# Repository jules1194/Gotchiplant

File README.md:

# Gotchiplant
Este proyecto busca implementar las funciones de una planta inteligente.

## Diagrama de caja negra sin solución tecnológica

## Diagrama de caja negra tecnológico

## Diseños realizados en clase

## Implementación 

### Esquematico circuital Gotchiplant

### Ruteo de las pistas en Kicad

### Diseño de la PCB en 3D

### PCB Real Terminada

## Pruebas realizadas durante la ejecución del proyecto

### Prueba Lectura de datos Arduino IDE  y salida Display
https://github.com/jules1194/Gotchiplant/assets/137961658/6f60a92b-0001-46fb-bf46-45bb00d068b1

### Conexión sensores y Arduino Nano a la PCB

### Prueba Simulación Código en Arduinio IDE
https://github.com/jules1194/Gotchiplant/assets/137961658/443aca30-f3b6-4041-8bca-e2bd3c89cd1e

### Prueba ensamble sensores, arduino nano y PCB con alimentación externa
https://github.com/jules1194/Gotchiplant/assets/137961658/406dce42-54d8-423b-a3e7-269711841c6a

## Videos sobre la implementación final del proyecto

### Explicación sobre la ubicación de los sensores de Gotchiplant
https://github.com/jules1194/Gotchiplant/assets/137961658/88809492-0296-4c42-850c-8ad4974c118a

### Funcionamiento Gotchiplant
https://github.com/jules1194/Gotchiplant/assets/137961658/c117f062-664b-49f6-9f2e-c704b0ddebe9

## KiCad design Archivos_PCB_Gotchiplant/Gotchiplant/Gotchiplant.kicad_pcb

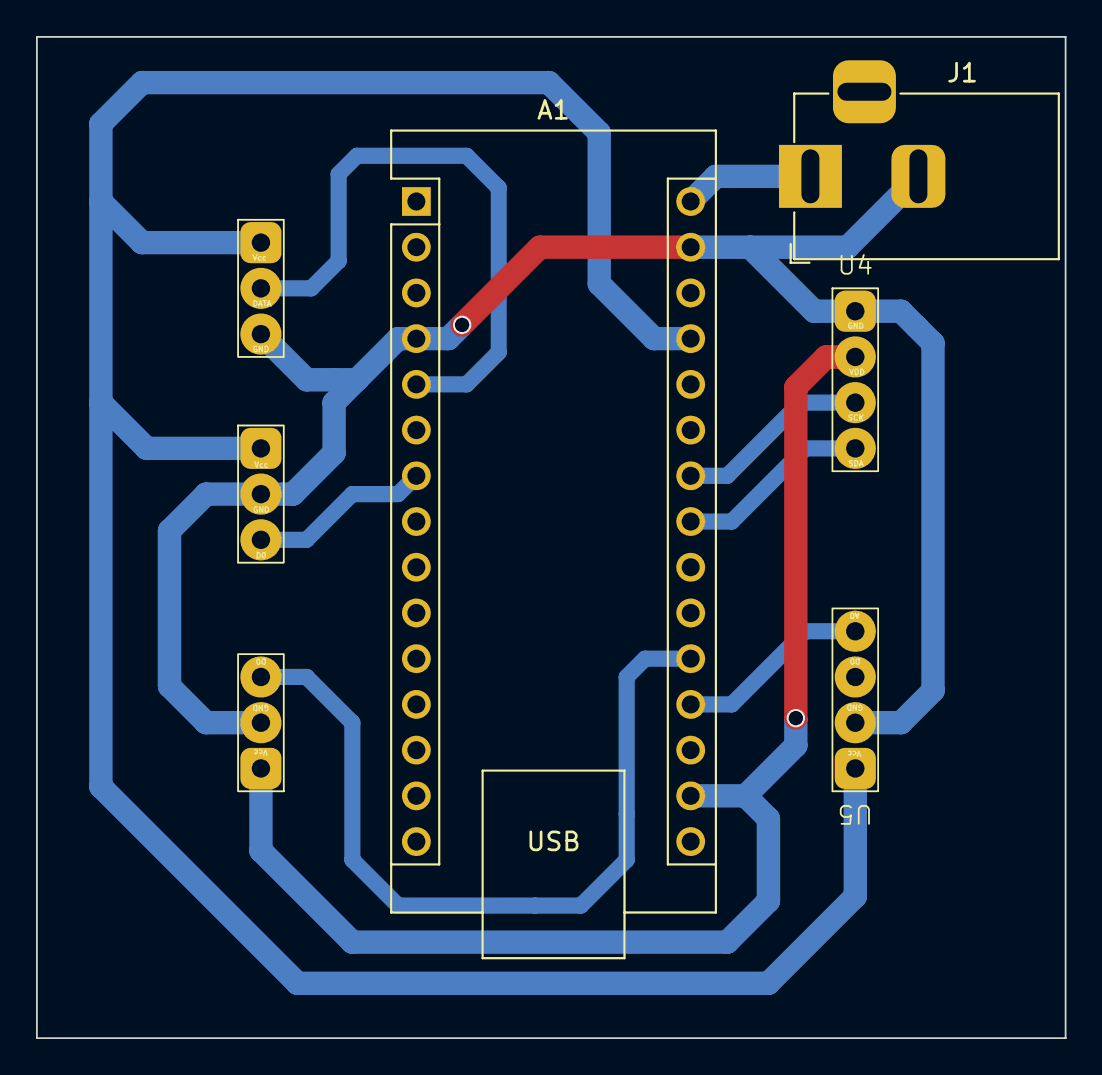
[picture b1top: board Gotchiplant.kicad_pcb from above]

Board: 2 copper layers, 57.1 x 55.6 mm, 7 parts (0 on the bottom side), 10 nets.

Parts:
A1: Arduino_Nano_v3.x; Arduino_Nano
J1: Jack-DC; BarrelJack_Horizontal
U2: DHT11
U3: LDR_Module_LM393; LDR Module LM393
U4: Display_LCD_OLED
U5: FC_28_SM_Sensor; FC_28_SM Sensor
U6: Vibration_Module_SW 420; Vibration_Module_SW420

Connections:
+5V: A1.30 (VIN), J1.1
GND: A1.4 (GND), A1.29 (GND), J1.2, U2.3 (GND), U3.2 (GND), U4.1 (GND), U5.2 (GND), U6.2 (GND)
unnamed: A1.17 (3V3), U4.2 (VDD), U6.1 (Vcc)
unnamed: A1.27 (+5V), U2.1 (Vcc), U3.1 (Vcc), U5.1 (Vcc)
unnamed: A1.19 (A0), U5.4 (A0)
unnamed: A1.20 (A1), U6.3 (D0)
unnamed: A1.23 (A4), U4.4 (SDA)
unnamed: A1.24 (A5), U4.3 (SCK)
unnamed: A1.5 (D2), U2.2 (DATA)
unnamed: A1.7 (D4), U3.3 (D0)

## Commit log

2023-06-28 Add files via upload
    Descripción:
    Este código de Arduino utiliza varios módulos para sensar y monitorear las condiciones ambientales de una planta. Se emplean sensores de humedad del suelo, temperatura y humedad, y luz para obtener d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
2023-06-28 Create Archivos_PCB_Gotchiplant
2023-06-28 Create Archivos Kicad
    En esta carpeta se encuentra los archivos relacionados con la elaboración del circuito impreso para el funcionamiento de los sensores de humedad, temperatura y luz junto con la placa de desarrollo Ar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
2023-06-28 Create Modelado 3D carcasa
    Archivo 3D de la carcasa del proyecto Gotchiplant, en este compartimento se van a ensamblar todos los componentes que hacen posible la portabilidad y funcionamiento del proyecto.
2023-06-28 Create Pruebas de los sensores en protoboard
    Recopilación de las pruebas realizadas con cada uno de los sensores necesarios para el funcionamiento del proyecto.
2023-06-28 Create Funcionamiento Gotchiplant
    Video de funcionamiento del proyecto Gotchiplant, acompañado de una explicación sobre sus componentes y el desarrollo del proyecto.
2023-06-28 Add files via upload
    Prototipo carcasa Gotchiplant
2023-06-28 Add files via upload
    Archivo 3D en formato .stl de la carcasa del proyecto Gotchiplant, en este se van a ensamblar todos los componentes que hacen posible la portabilidad del proyecto.
2023-06-28 Add files via upload
    Poster presentación proyecto Gotchiplant
2023-06-28 Add files via upload
    Archivos de diseño del circuito impreso para el proyecto Gotchiplant usando el software Kicad.
